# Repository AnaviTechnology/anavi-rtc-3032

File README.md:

# ANAVI RTC 3032

Open source hardware real-time clock module with I2C bus interface built around RV-3032-C7.

ANAVI RTC 3032 has been designed with [the cross platform and open source electronics design automation suite KiCad](https://kicad.org/).

# License

The project is released under the [Creative Commons Attribution-ShareAlike 4.0 International (CC BY-SA 4.0)](https://creativecommons.org/licenses/by-sa/4.0/).

Note: This is a human-readable summary of (and not a substitute for) the [license](https://creativecommons.org/licenses/by-sa/4.0/legalcode).

You are free to:

Share — copy and redistribute the material in any medium or format Adapt — remix, transform, and build upon the material for any purpose, even commercially. The licensor cannot revoke these freedoms as long as you follow the license terms. Under the following terms:

Attribution — You must give appropriate credit, provide a link to the license, and indicate if changes were made. You may do so in any reasonable manner, but not in any way that suggests the licensor endorses you or your use. ShareAlike — If you remix, transform, or build upon the material, you must distribute your contributions under the same license as the original. No additional restrictions — You may not apply legal terms or technological measures that legally restrict others from doing anything the license permits. Notices:

You do not have to comply with the license for elements of the material in the public domain or where your use is permitted by an applicable exception or limitation. No warranties are given. The license may not give you all of the permissions necessary for your intended use. For example, other rights such as publicity, privacy, or moral rights may limit how you use the material.

You will have to provide a link to the original creator of the project http://www.anavi.technology on any documentation or website.

Credit can be attributed through a link to the creator website: http://www.anavi.technology

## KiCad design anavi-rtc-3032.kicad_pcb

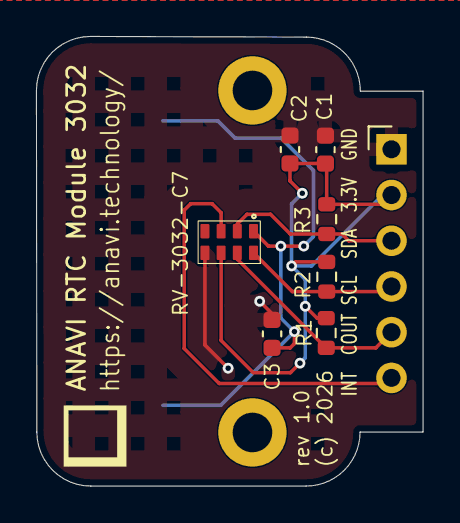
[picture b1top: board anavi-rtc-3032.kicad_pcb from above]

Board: 2 copper layers, 21.5 x 25.0 mm, 9 parts (1 on the bottom side), 7 nets.

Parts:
C1: 10uF; C_0603_1608Metric
C2, C3: 100nF; C_0603_1608Metric
CR1216/CR1220 Battery: Battery_Cell; BatteryHolder_Keystone_3000_1x12mm
J1: Conn_01x06_Pin; PinHeader_1x06_P2.54mm_Horizontal-mod
R1: 10k; R_0603_1608Metric
R2, R3: 4.7k; R_0603_1608Metric
RV-3032-C7: RV-3032

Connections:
+3V3: C1.1, C2.2, J1.2, R1.2, R2.1, R3.1, RV-3032-C7.6 (VDD)
GND: C1.2, C2.1, C3.1, CR1216/CR1220 Battery.2 (-), J1.1, RV-3032-C7.5 (VSS)
I2C_SCL_OTHER: J1.4, R2.2, RV-3032-C7.8 (SCL)
I2C_SDA_OTHER: J1.3, R3.2, RV-3032-C7.2 (SDA)
unnamed: C3.2, CR1216/CR1220 Battery.1 (+), RV-3032-C7.1 (VBACKUP)
RTC_INT: J1.6, RV-3032-C7.3 (~INT)
RTC_SQW: J1.5, R1.1, RV-3032-C7.7 (CLKOUT)

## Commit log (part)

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2026-06-06 Initial commit
    Open source hardware real-time clock module with RV-3032-C7.
2026-06-07 Fix ERC issues in schematics
    Fix issues in the Electrical Rules Checker (ERC) for the schematics.
2026-06-07 .gitignore: Ignore *.lck
    Add *.lck to the list of temporary files to ignore.
2026-06-07 lib: Add PinHeader_1x06_P2.54mm_Horizontal-mod
    Add a modified version of PinHeader_1x06_P2.54mm_Horizontal.
2026-06-07 logo.pretty: Add the logo
    Add the ANAVI Technology logo.
2026-06-07 Printed Circuit Board
    Add the PCB design for hardware revision 1.0.
2026-06-07 Add fabrication details
    Adjust the PCB layers to add fabrication details.
2026-06-08 Change PCB output
    Change the shape of the PCB outline and adjust labels.

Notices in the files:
anavi-rtc-3032.kicad_pcb:
(c) 2026
